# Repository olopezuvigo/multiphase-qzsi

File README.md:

# Quasi-Impedance-Source Inverter Boards for Multiphase Motor Drive Applications

A set of KiCad projects for designing and documenting a multiphase **Quasi-Z-Source Inverter (QZSI)** for multiphase motor drive applications.

This work was supported by [MCIN/AEI/10.13039/501100011033/FEDER, UE](https://www.aei.gob.es/en) under Project [PID2021-124136OB-I00](http://olopez.webs.uvigo.es/pgc2021.html).

## Overview

This repository contains the complete KiCad design files for a multiphase QZSI, intended for a multiphase QZSI motor drive.
The multiphase QZSI is comprised of **two** types of boards:
- **Z-source board**: documented in the KiCad project [`Modular_qZSI_Z_board`](https://github.com/olopezuvigo/multiphase-qzsi/tree/main/Modular_qZSI_Z_board)
- **Half-bridge boards**: documented in the KiCad project [`Modular_qZSI_leg_board`](https://github.com/olopezuvigo/multiphase-qzsi/tree/main/Modular_qZSI_leg_board)

An $n$-phase QZSI can be built with $n$ **Half-Bridge Leg Boards** and at least one **Z-Source Board**.

### Z-Source Board

This board is the core impedance network of the qZSI. Its main job is to provide buck-boost voltage conversion. It contains two large banks of capacitors (`C1 Capacitor Bank` and `C2 Capacitor Bank`) and provides connection points for two external inductors (`L1` and `L2`). Together, these components create a variable DC bus that powers the inverter legs.

### Half-Bridge Leg Board

This board is a single half-bridge, representing one phase of the inverter. It's an interface board that connects to an external power stage module (`EVAL-ADUM4146WHB1Z`) where the actual MOSFETs and drivers are located.

### System Operation & Modularity

The system functions by using the Z-source network to allow controlled **shoot-through** states in the inverter legs. This unique feature boosts the DC bus voltage without causing damage. The inverter legs then use this boosted DC voltage to create the final AC output.

The key feature is **modularity**. By connecting multiple leg boards to the central Z-source board, the system can be configured as a single-phase, three-phase, or other multiphase inverters.

## Project Structure

| File/Folder         | Description                                      |
|---------------------|--------------------------------------------------|
| `*/*.kicad_pro`     | KiCad project file                               |
| `*/*.sch`           | Schematic file(s)                                |
| `*/*.kicad_pcb`     | PCB layout                                       |
| `*/*.lib` / `*.dcm` | Custom symbol libraries (if any)                 |
| `*/*.pretty`        | Custom footprint libraries (if any)              |
| `*/*.packages3D`    | 3D models                                        |
| `*/Documentation`   | Documentation (PDFs, images, datasheets, etc.)   |

## Getting Started

### Prerequisites

- [KiCad](https://www.kicad.org/download/) (version 8.03 or newer)

### Opening the Project

1. Clone this repository:
   ```sh
   git clone https://github.com/olopezuvigo/multiphase-qzsi.git

## References
[1] Óscar López Sánchez. (2025). olopezuvigo/multiphase-qzsi: v1.2 (v1.2). Zenodo. [doi: 10.5281/zenodo.17264291](https://doi.org/10.5281/zenodo.17264291)

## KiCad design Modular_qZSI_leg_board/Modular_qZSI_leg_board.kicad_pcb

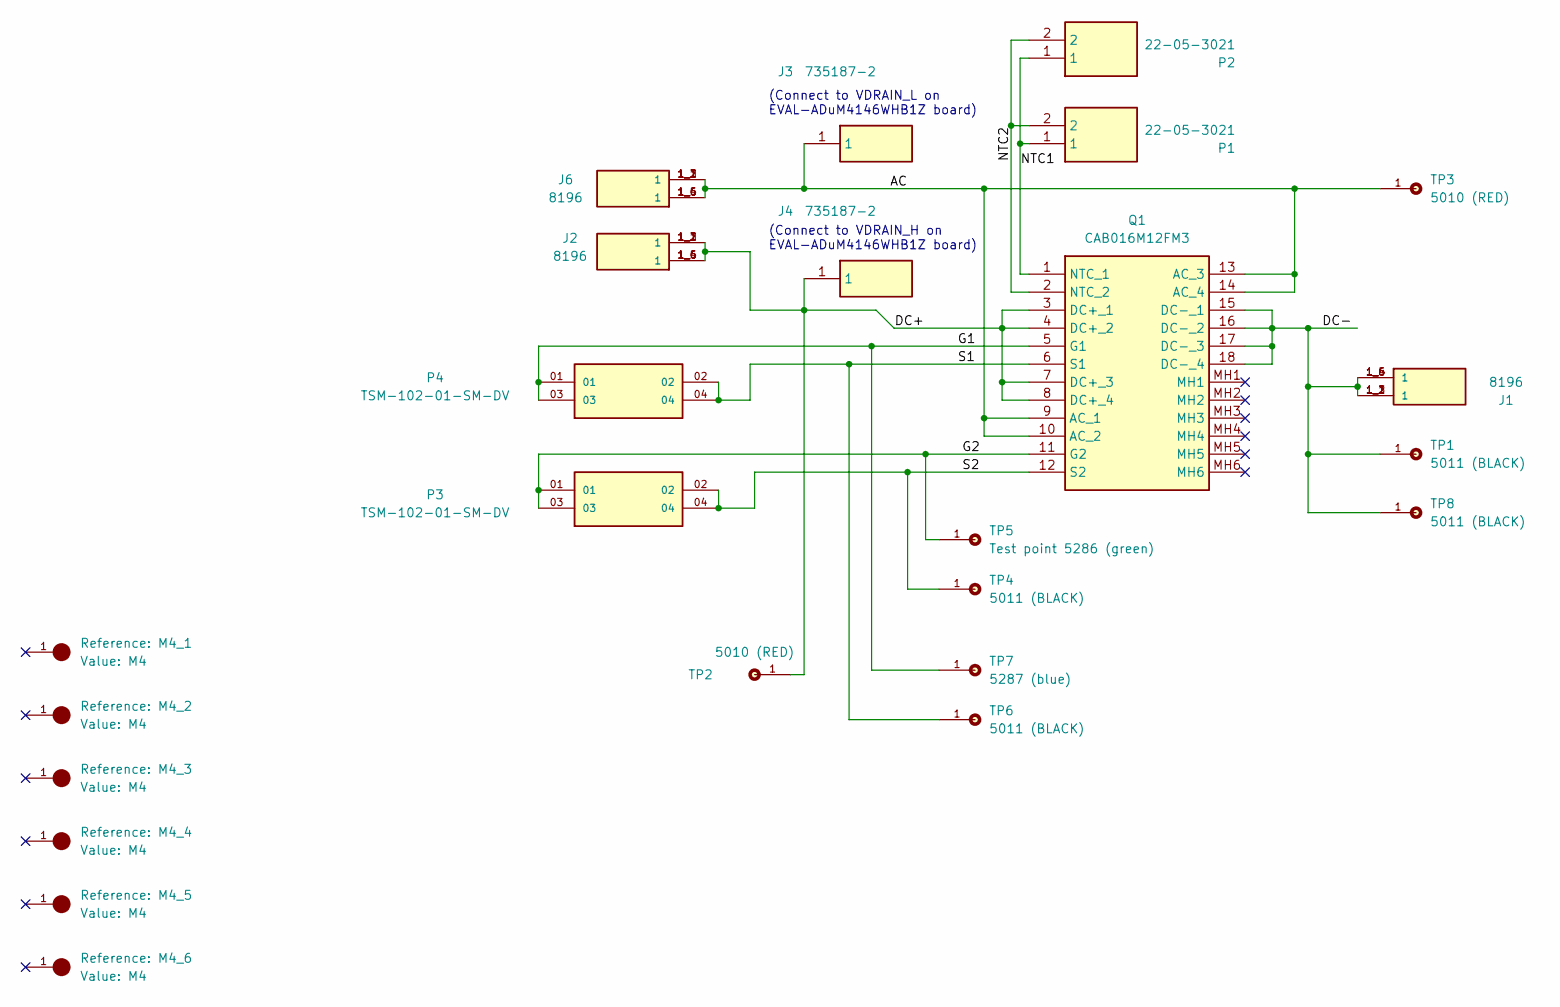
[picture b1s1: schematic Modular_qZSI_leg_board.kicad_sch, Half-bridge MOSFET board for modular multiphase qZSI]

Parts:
J1, J2, J6: 8196; KEYSTONE_8196; PARTREV D
J3, J4: 735187-2; TE_CONNECTIVITY_7351872; Mouser Part Number 571-735187-2
M4_1, M4_2, M4_3, M4_4, M4_5, M4_6: M4; M4_Hole; PARTREV F
P1, P2: 22-05-3021; Connector_for_NTC_signal_22-05-3021; Mouser Part Number 538-22-05-3021
P3, P4: TSM-102-01-SM-DV; SAMTEC_TSM-102-01-SM-DV
Q1: CAB016M12FM3; CAB016M12FM3_with_insert_pins_no_DC_dridge; Mouser Part Number 941-CAB016M12FM3
TP1, TP4, TP6, TP8: 5011 (BLACK); Test_pin_KEYSTONE_5011; PARTREV F
TP2, TP3: 5010 (RED); Test_pin_KEYSTONE_5010 (red); PARTREV F; DigiKey_Part_Number 36-5010-ND
TP5: Test point 5286 (green); Test_pin_KEYSTONE_5286
TP7: 5287 (blue); Test_pin_KEYSTONE_5287

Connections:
/AC: J3.1, J6.1_1 (1), J6.1_2 (1), J6.1_3 (1), J6.1_4 (1), J6.1_5 (1), J6.1_6 (1), Q1.9 (AC_1), Q1.10 (AC_2), Q1.13 (AC_3), Q1.14 (AC_4), TP3.1
/DC+: J2.1_1 (1), J2.1_2 (1), J2.1_3 (1), J2.1_4 (1), J2.1_5 (1), J2.1_6 (1), J4.1, Q1.3 (DC+_1), Q1.4 (DC+_2), Q1.7 (DC+_3), Q1.8 (DC+_4), TP2.1
/DC-: J1.1_1 (1), J1.1_2 (1), J1.1_3 (1), J1.1_4 (1), J1.1_5 (1), J1.1_6 (1), Q1.15 (DC-_1), Q1.16 (DC-_2), Q1.17 (DC-_3), Q1.18 (DC-_4), TP1.1, TP8.1
/G1: P4.01, P4.03, Q1.5 (G1), TP7.1
/G2: P3.01, P3.03, Q1.11 (G2), TP5.1
/NTC1: P1.1, P2.1, Q1.1 (NTC_1)
/NTC2: P1.2, P2.2, Q1.2 (NTC_2)
/S1: P4.02, P4.04, Q1.6 (S1), TP6.1
/S2: P3.02, P3.04, Q1.12 (S2), TP4.1

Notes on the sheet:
(Connect to VDRAIN_L on EVAL-ADuM4146WHB1Z board)
(Connect to VDRAIN_H on EVAL-ADuM4146WHB1Z board)

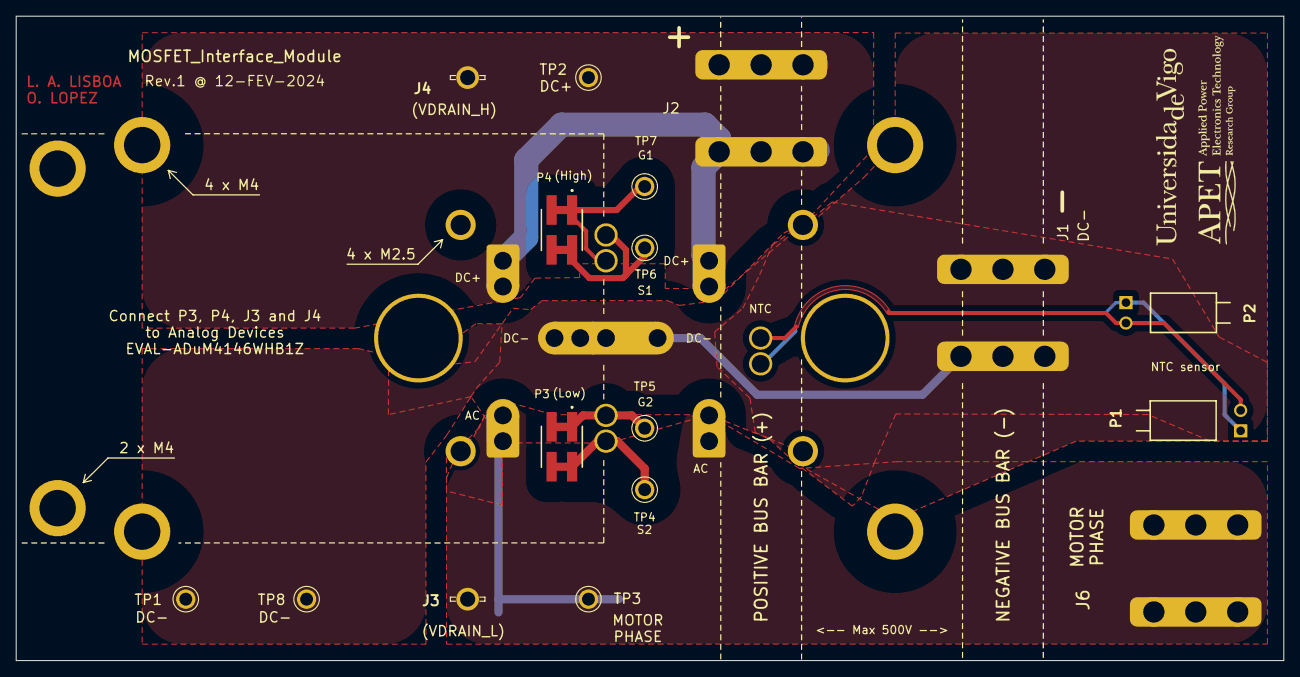
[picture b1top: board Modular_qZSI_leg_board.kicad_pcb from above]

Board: 2 copper layers, 157.4 x 80.0 mm, 24 parts (0 on the bottom side), 9 nets.

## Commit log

2025-10-03 Let's go
2025-10-03 Kicad projects archived with https://github.com/esynr3z/kicad-archive-project
2025-10-03 Readme and license added
2025-10-04 Pictures added
